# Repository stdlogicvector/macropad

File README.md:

# MacroPad

A custom built 3x4 key macropad with encoders.

More Info on this 

## Circuit Board

The circuit board is designed in Eagle.
For easy manufacturing, the gerber-files and SMT production files are included.

The BOM and SMT placement file (CPL) are formatted for use with JLCPCB.

Apart from the keys, encoders, the USB-connector and the LED matrix driver all parts can be populated by JLCPCB.
The schematic contains the LCSC partnumbers in the attributes of each part.

### Keys

All keys compatible with Cherry MX 2 or 3 pin should fit the board.

### Encoders

The encoders a standard rotary encoders, just search ebay/aliexpress/amazon or your local electronics dealer.

## QMK Configuration

The folder qmk_config contains the configuration and code to build QMK for the NumPad.
Just put this folder in qmk/keyboards and run

```
make macropad/v1:default
```	
	
## Case

The case can be 3D printed in two parts.
There are holes for heat-set M3 threaded inserts to hold the PCB and M2 threaded inserts to hold the plate.

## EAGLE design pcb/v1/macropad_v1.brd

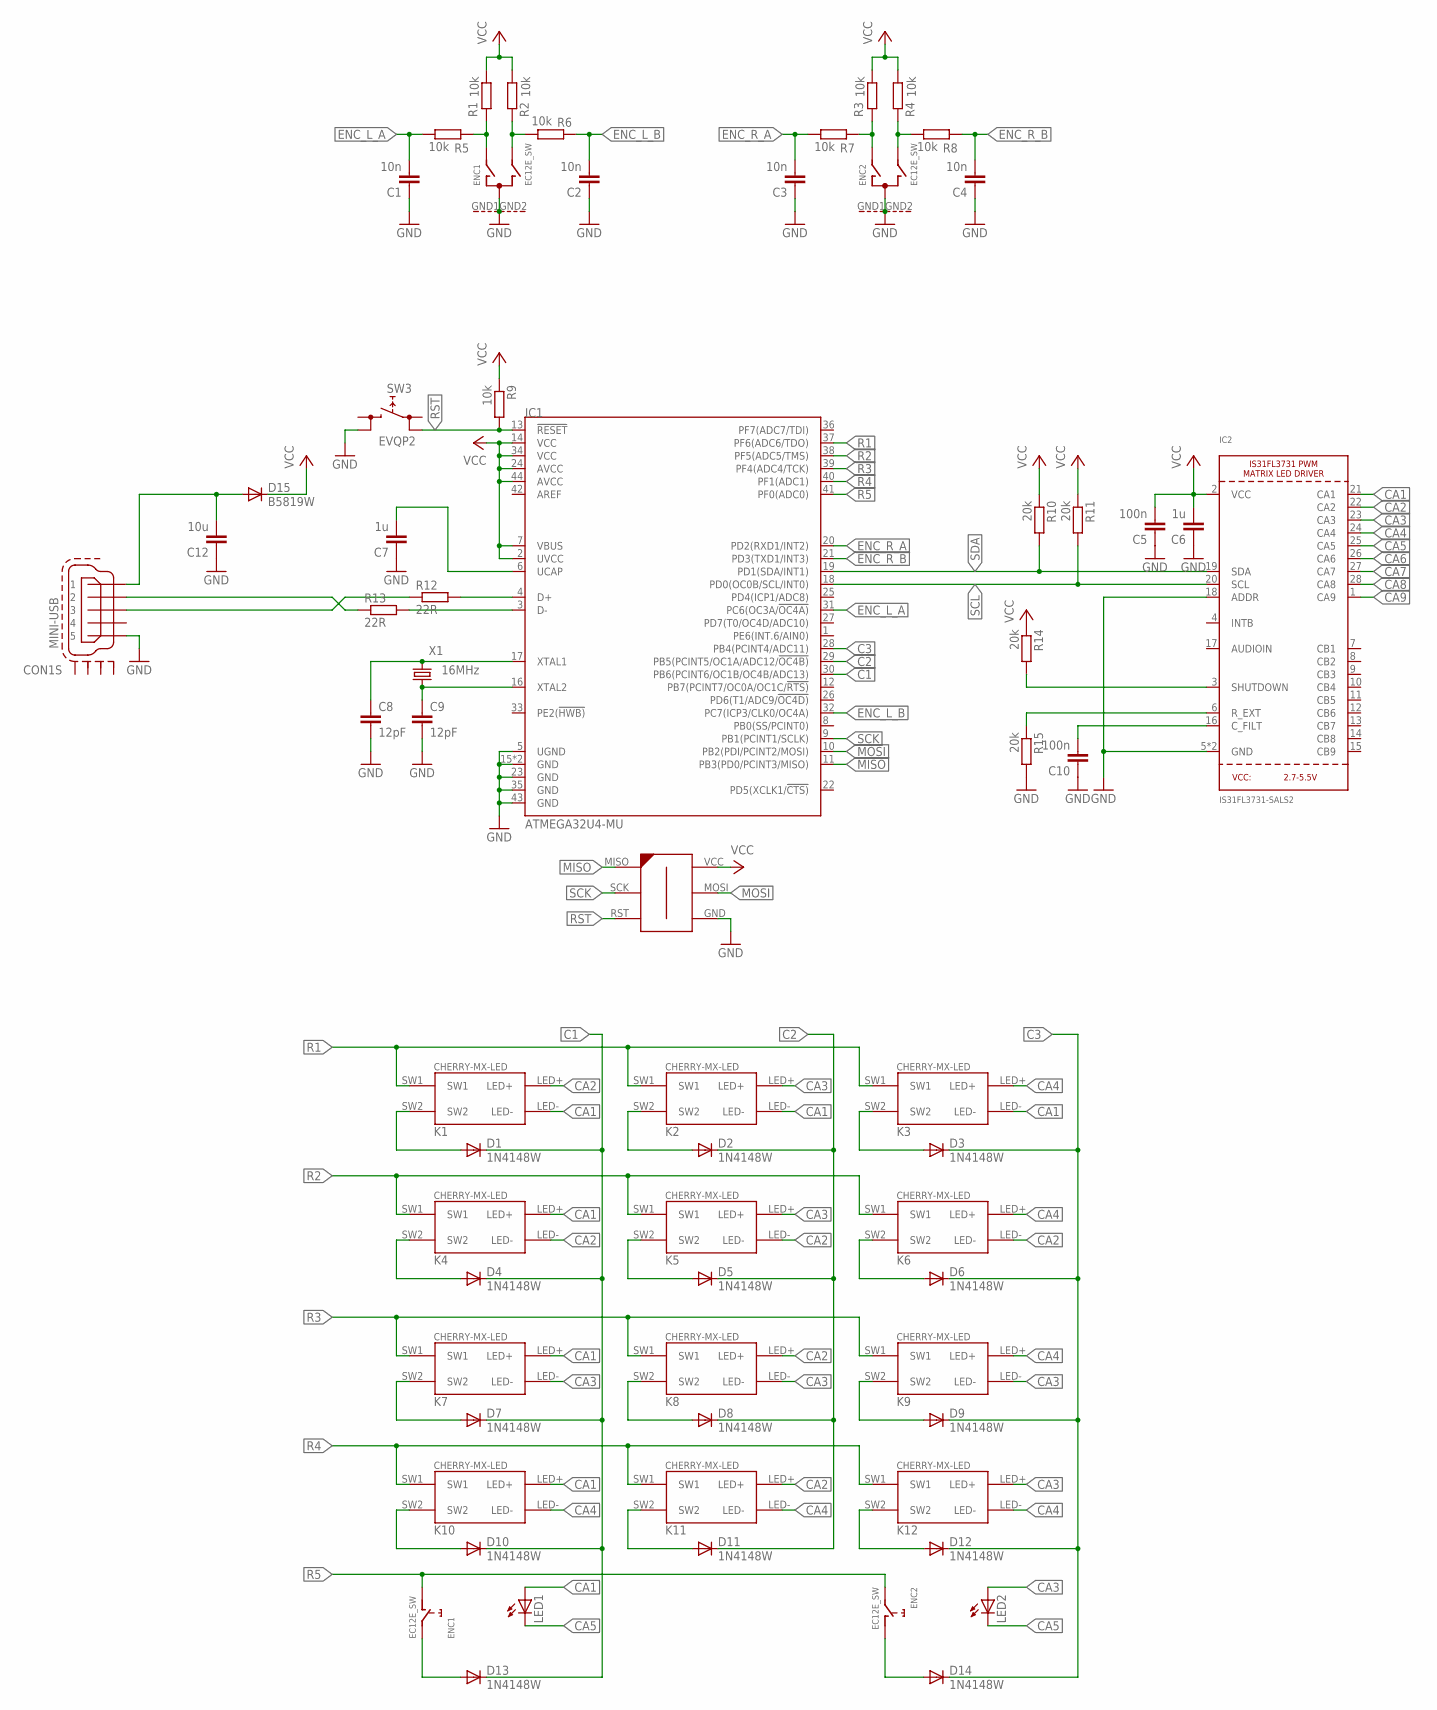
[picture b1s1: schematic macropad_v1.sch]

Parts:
C1, C2, C3, C4: 10n; C0603; LCSC C57112
C5, C10: 100n; C0603; LCSC C14663
C6, C7: 1u; C0603; LCSC C15849
C8, C9: 12pF; C0603; LCSC C38523
C12: 10u; C0603; LCSC C19702
CON1: MINI-USB; 32005-201
D1, D2, D3, D4, D5, D6, D7, D8, D9, D10, D11, D12, D13, D14: 1N4148W; SOD123; LCSC C81598
D15: B5819W; SOD123; LCSC C8598
ENC1, ENC2: EC12E_SW; ALPS_EC12E_SW
IC1: ATMEGA32U4-MU; QFN44G-0.5-7X7MM; LCSC C112161
IC2: IS31FL3731-SALS2; QFN28_4MM_0.4MM
K1, K2, K3, K4, K5, K6, K7, K8, K9, K10, K11, K12: CHERRY-MX-LED
LED1, LED2: LED3MM
R1, R2, R3, R4, R5, R6, R7, R8, R9: 10k; R0603; LCSC C25804
R10, R11, R14, R15: 20k; R0603; LCSC C4184
R12, R13: 22R; R0603; LCSC C23345
SW3: EVQP2; FARNELL 2079559
U$1: AVR-ISP-6-EDGE; 6PAD_ISP
X1: 16MHz; 3.2X2.5_KX-7; LCSC C13738

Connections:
C1: D1.C, D4.C, D7.C, D10.C, D13.C, IC1.30 (PB6(PCINT6/OC1B/OC4B/ADC13))
C2: D2.C, D5.C, D8.C, D11.C, IC1.29 (PB5(PCINT5/OC1A/ADC12/!OC4B))
C3: D3.C, D6.C, D9.C, D12.C, D14.C, IC1.28 (PB4(PCINT4/ADC11))
CA1: IC2.21 (CA1), K1.LED-, K2.LED-, K3.LED-, K4.LED+, K7.LED+, K10.LED+, LED1.A
CA2: IC2.22 (CA2), K1.LED+, K4.LED-, K5.LED-, K6.LED-, K8.LED+, K11.LED+
CA3: IC2.23 (CA3), K2.LED+, K5.LED+, K7.LED-, K8.LED-, K9.LED-, K12.LED+, LED2.A
CA4: IC2.24 (CA4), K3.LED+, K6.LED+, K9.LED+, K10.LED-, K11.LED-, K12.LED-
CA5: IC2.25 (CA5), LED1.K (C), LED2.K (C)
CA6: IC2.26 (CA6)
CA7: IC2.27 (CA7)
CA8: IC2.28 (CA8)
CA9: IC2.1 (CA9)
ENC_L_A: C1.2, IC1.31 (PC6(OC3A/!OC4A)), R5.1
ENC_L_B: C2.2, IC1.32 (PC7(ICP3/CLK0/OC4A)), R6.2
ENC_R_A: C3.2, IC1.20 (PD2(RXD1/INT2)), R7.1
ENC_R_B: C4.2, IC1.21 (PD3(TXD1/INT3)), R8.2
GND: C1.1, C2.1, C3.1, C4.1, C5.1, C6.1, C7.1, C8.2, C9.2, C10.1, C12.1, CON1.5, ENC1.C, ENC1.GND1 (G), ENC1.GND2 (G), ENC2.C, ENC2.GND1 (G), ENC2.GND2 (G), IC1.5 (UGND), IC1.15 (GND), IC1.23 (GND), IC1.35 (GND), IC1.43 (GND), IC1.TAB (GND), IC2.5 (GND), IC2.18 (ADDR), IC2.THERMAL (GND), R15.2, SW3.2 (1), U$1.GND
MISO: IC1.11 (PB3(PD0/PCINT3/MISO)), U$1.MISO
MOSI: IC1.10 (PB2(PDI/PCINT2/MOSI)), U$1.MOSI
unnamed: D1.A, K1.SW2
unnamed: D4.A, K4.SW2
unnamed: D7.A, K7.SW2
unnamed: D10.A, K10.SW2
unnamed: D5.A, K5.SW2
unnamed: D2.A, K2.SW2
unnamed: D8.A, K8.SW2
unnamed: D11.A, K11.SW2
unnamed: D12.A, K12.SW2
unnamed: D9.A, K9.SW2
unnamed: D6.A, K6.SW2
unnamed: D3.A, K3.SW2
unnamed: IC1.4 (D+), R12.2
unnamed: IC1.3 (D-), R13.2
unnamed: CON1.2, R13.1
unnamed: CON1.3, R12.1
unnamed: C8.1, IC1.17 (XTAL1), X1.3 (2)
unnamed: C12.2, CON1.1, D15.A
unnamed: C9.1, IC1.16 (XTAL2), X1.1
unnamed: C7.2, IC1.6 (UCAP)
unnamed: IC2.6 (R_EXT), R15.1
unnamed: D13.A, ENC1.E (2)
unnamed: D14.A, ENC2.D (1)
unnamed: C10.2, IC2.16 (C_FILT)
unnamed: IC2.3 (SHUTDOWN), R14.2
unnamed: ENC1.A, R1.2, R5.2
unnamed: ENC2.A, R3.2, R7.2
unnamed: ENC1.B, R2.2, R6.1
unnamed: ENC2.B, R4.2, R8.1
R1: IC1.37 (PF6(ADC6/TDO)), K1.SW1, K2.SW1, K3.SW1
R2: IC1.38 (PF5(ADC5/TMS)), K4.SW1, K5.SW1, K6.SW1
R3: IC1.39 (PF4(ADC4/TCK)), K7.SW1, K8.SW1, K9.SW1
R4: IC1.40 (PF1(ADC1)), K10.SW1, K11.SW1, K12.SW1
R5: ENC1.D (1), ENC2.E (2), IC1.41 (PF0(ADC0))
RST: IC1.13 (!RESET), R9.2, SW3.3 (0), U$1.RST
SCK: IC1.9 (PB1(PCINT1/SCLK)), U$1.SCK
SCL: IC1.18 (PD0(OC0B/SCL/INT0)), IC2.20 (SCL), R11.2
SDA: IC1.19 (PD1(SDA/INT1)), IC2.19 (SDA), R10.2
VCC: C5.2, C6.2, D15.C, IC1.2 (UVCC), IC1.7 (VBUS), IC1.14 (VCC), IC1.24 (AVCC), IC1.34 (VCC), IC1.44 (AVCC), IC2.2 (VCC), R1.1, R2.1, R3.1, R4.1, R9.1, R10.1, R11.1, R14.1, U$1.VCC

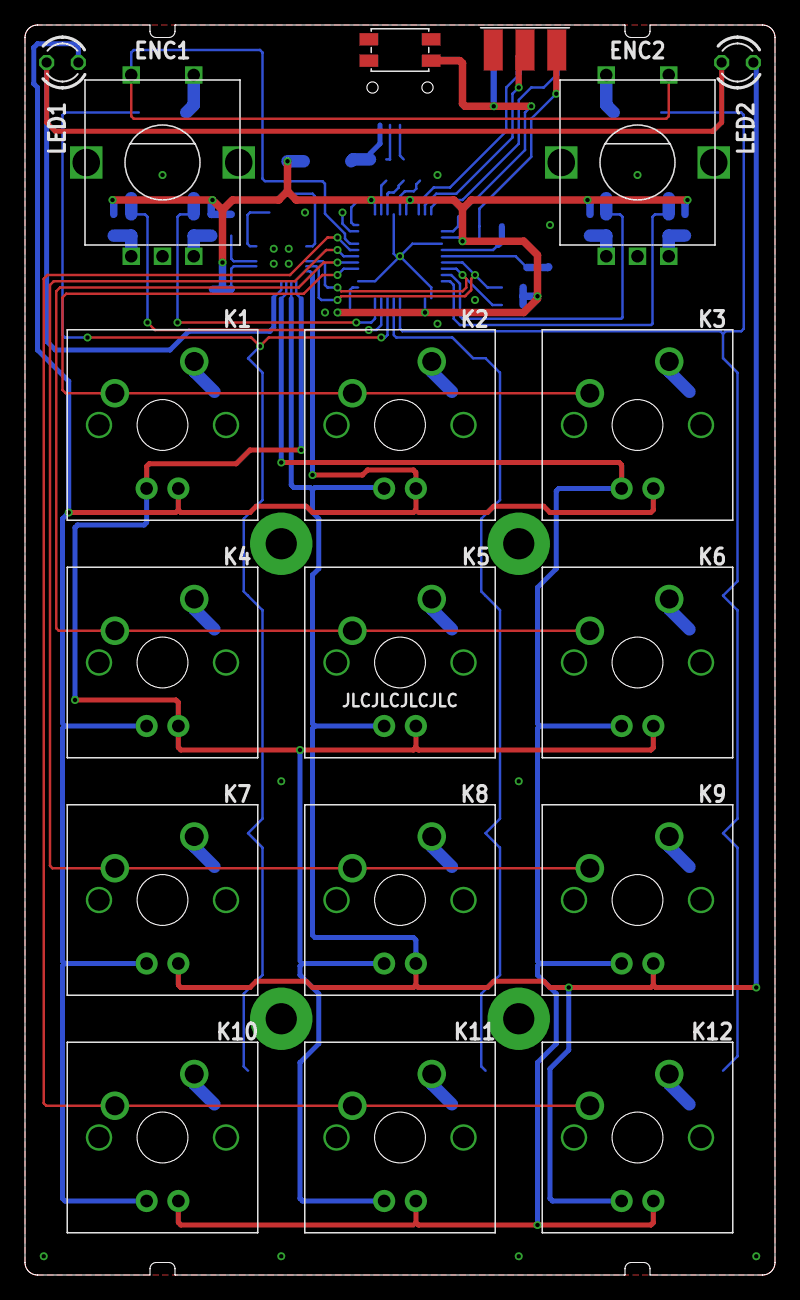
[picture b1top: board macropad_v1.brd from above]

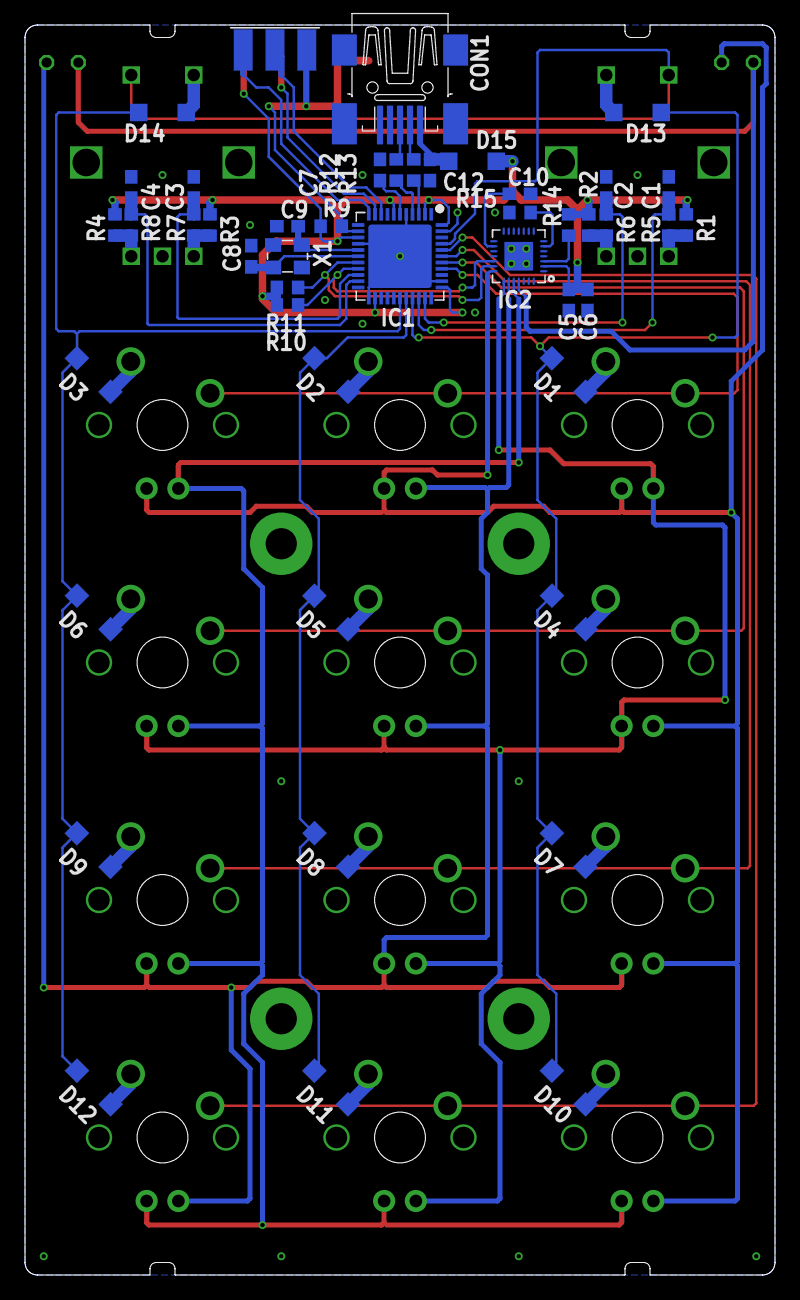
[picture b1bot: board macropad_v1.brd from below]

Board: 2 copper layers, 60.0 x 100.0 mm, 63 parts (46 on the bottom side), 54 nets.

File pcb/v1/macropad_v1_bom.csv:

Comment,Designator,Footprint,LCSC
1N4148W,"D1, D2, D3, D4, D5, D6, D7, D8, D9, D10, D11, D12, D13, D14",SOD-123,C81598
1uF,"C6, C7",0603_C,C15849
10k,"R1, R2, R3, R4, R5, R6, R7, R8, R9",0603_R,C25804
10nF,"C1, C2, C3, C4",0603_C,C57112
10uF,C12,0603_C,C19702
12pF,"C8, C9",0603_C,C38523
16MHz,X1,SMD-3225_4P,C13738
20k,"R10, R11, R14, R15",0603_R,C4184
22R,"R12, R13",0603_R,C23345
100nF,"C5, C10",0603_C,C14663
ATMEGA32U4-MU,IC1,QFN-44_EP_7x7x0.5P,C112161
B5819W,D15,SOD-123,C8598

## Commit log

2019-12-12 First Revision
2019-12-13 fix(readme):Imgur Links
2019-12-13 fix(readme): Imgur Link

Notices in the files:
parts and their libraries:
crystal-geyer_V1_0: Copyright: Geyer-Electronic
microbuilder: This work is placed in the public domain, and may be freely used for commercial and non-commercial work with the following conditions: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
